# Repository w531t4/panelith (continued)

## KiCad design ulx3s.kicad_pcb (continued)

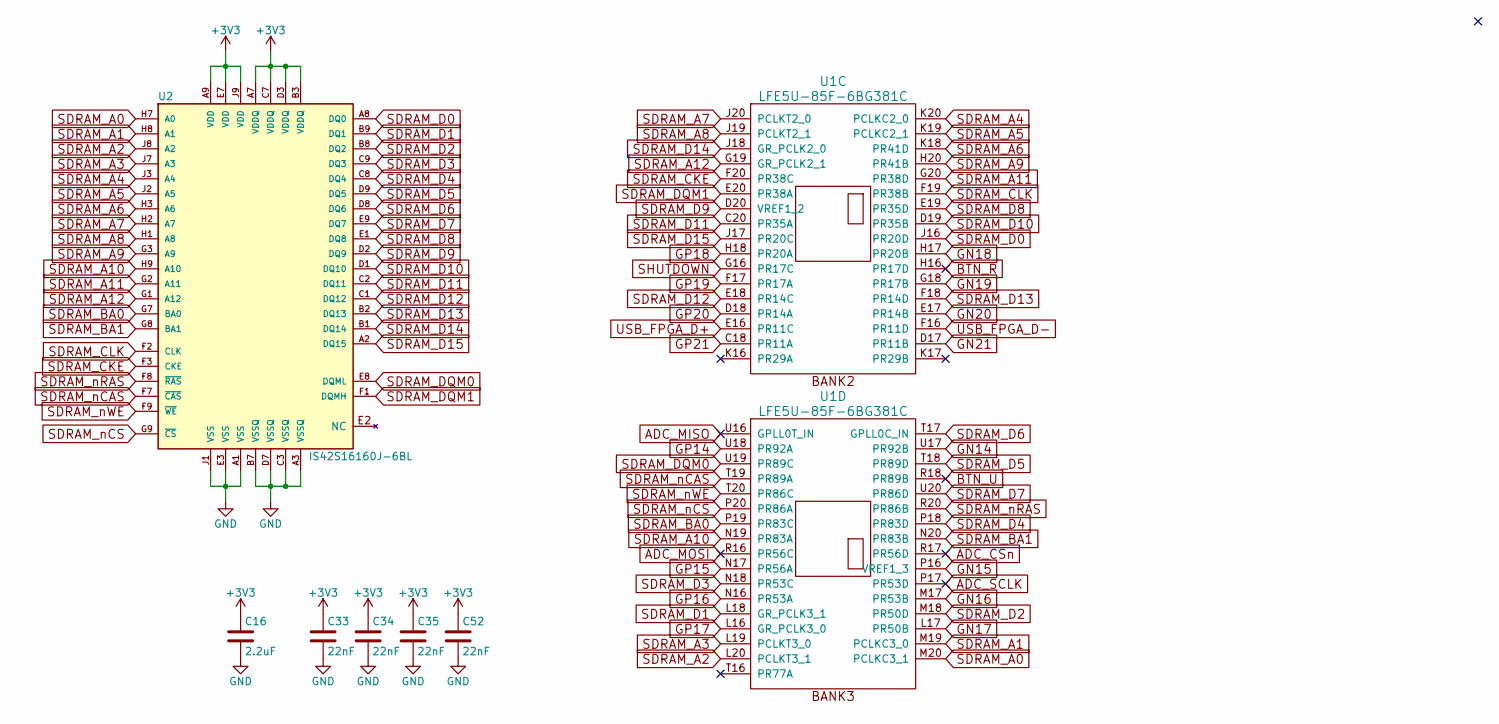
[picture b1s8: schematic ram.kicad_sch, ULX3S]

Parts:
C16: 2.2uF; C_0805_2012Metric; MPN CC0805MRX5R6BB225; LCSC C87995
C33, C34, C35, C52: 22nF; C_0603_1608Metric; MPN CC0603JRX7R8BB223; LCSC C107137
U1: LFE5U-85F-6BG381C; BGA-381_pitch0.8mm_dia0.4mm; MPN LFE5U-85F-6BG381C; LCSC C446029
U2: IS42S16160J-6BL; BGA54C80P9X9_800X800X120; MPN 870-42S16160J6BL; Mouser 870-IS42S16160G7TLTR

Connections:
+3V3: C16.1, C33.1, C34.1, C35.1, C52.1, U2.A7 (VDDQ), U2.A9 (VDD), U2.B3 (VDDQ), U2.C7 (VDDQ), U2.D3 (VDDQ), U2.E7 (VDD), U2.J9 (VDD); also elsewhere on the board
ADC_CSn: U1.R17 (PR56D)
ADC_MISO: U1.U16 (GPLL0T_IN)
ADC_MOSI: U1.R16 (PR56C)
ADC_SCLK: U1.P17 (PR53D)
BTN_R: U1.H16 (PR17D)
BTN_U: U1.R18 (PR89B)
GN14: U1.U17 (PR92B)
GN15: U1.P16 (VREF1_3)
GN16: U1.M17 (PR53B)
GN17: U1.L17 (PR50B)
GN18: U1.H17 (PR20B)
GN19: U1.G18 (PR17B)
GN20: U1.E17 (PR14B)
GN21: U1.D17 (PR11B)
GND: C16.2, C33.2, C34.2, C35.2, C52.2, U2.A1 (VSS), U2.A3 (VSSQ), U2.B7 (VSSQ), U2.C3 (VSSQ), U2.D7 (VSSQ), U2.E3 (VSS), U2.J1 (VSS); also elsewhere on the board
GP14: U1.U18 (PR92A)
GP15: U1.N17 (PR56A)
GP16: U1.N16 (PR53A)
GP17: U1.L16 (GR_PCLK3_0)
GP18: U1.H18 (PR20A)
GP19: U1.F17 (PR17A)
GP20: U1.D18 (PR14A)
GP21: U1.C18 (PR11A)
SDRAM_A0: U1.M20 (PCLKC3_1), U2.H7 (A0)
SDRAM_A1: U1.M19 (PCLKC3_0), U2.H8 (A1)
SDRAM_A2: U1.L20 (PCLKT3_1), U2.J8 (A2)
SDRAM_A3: U1.L19 (PCLKT3_0), U2.J7 (A3)
SDRAM_A4: U1.K20 (PCLKC2_0), U2.J3 (A4)
SDRAM_A5: U1.K19 (PCLKC2_1), U2.J2 (A5)
SDRAM_A6: U1.K18 (PR41D), U2.H3 (A6)
SDRAM_A7: U1.J20 (PCLKT2_0), U2.H2 (A7)
SDRAM_A8: U1.J19 (PCLKT2_1), U2.H1 (A8)
SDRAM_A9: U1.H20 (PR41B), U2.G3 (A9)
SDRAM_A10: U1.N19 (PR83A), U2.H9 (A10)
SDRAM_A11: U1.G20 (PR38D), U2.G2 (A11)
SDRAM_A12: U1.G19 (GR_PCLK2_1), U2.G1 (A12)
SDRAM_BA0: U1.P19 (PR83C), U2.G7 (BA0)
SDRAM_BA1: U1.N20 (PR83B), U2.G8 (BA1)
SDRAM_CKE: U1.F20 (PR38C), U2.F3 (CKE)
SDRAM_CLK: U1.F19 (PR38B), U2.F2 (CLK)
SDRAM_D0: U1.J16 (PR20D), U2.A8 (DQ0)
SDRAM_D1: U1.L18 (GR_PCLK3_1), U2.B9 (DQ1)
SDRAM_D2: U1.M18 (PR50D), U2.B8 (DQ2)
SDRAM_D3: U1.N18 (PR53C), U2.C9 (DQ3)
SDRAM_D4: U1.P18 (PR83D), U2.C8 (DQ4)
SDRAM_D5: U1.T18 (PR89D), U2.D9 (DQ5)
SDRAM_D6: U1.T17 (GPLL0C_IN), U2.D8 (DQ6)
SDRAM_D7: U1.U20 (PR86D), U2.E9 (DQ7)
SDRAM_D8: U1.E19 (PR35D), U2.E1 (DQ8)
SDRAM_D9: U1.D20 (VREF1_2), U2.D2 (DQ9)
SDRAM_D10: U1.D19 (PR35B), U2.D1 (DQ10)
SDRAM_D11: U1.C20 (PR35A), U2.C2 (DQ11)
SDRAM_D12: U1.E18 (PR14C), U2.C1 (DQ12)
SDRAM_D13: U1.F18 (PR14D), U2.B2 (DQ13)
SDRAM_D14: U1.J18 (GR_PCLK2_0), U2.B1 (DQ14)
SDRAM_D15: U1.J17 (PR20C), U2.A2 (DQ15)
SDRAM_DQM0: U1.U19 (PR89C), U2.E8 (DQML)
SDRAM_DQM1: U1.E20 (PR38A), U2.F1 (DQMH)
SDRAM_nCAS: U1.T19 (PR89A), U2.F7 (~CAS)
SDRAM_nCS: U1.P20 (PR86A), U2.G9 (~CS)
SDRAM_nRAS: U1.R20 (PR86B), U2.F8 (~RAS)
SDRAM_nWE: U1.T20 (PR86C), U2.F9 (~WE)
SHUTDOWN: U1.G16 (PR17C)
USB_FPGA_D+: U1.E16 (PR11C); also elsewhere on the board
USB_FPGA_D-: U1.F16 (PR11D); also elsewhere on the board

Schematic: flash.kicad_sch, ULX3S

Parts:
D28: 1N914; D_SOD-323_HandSoldering; MPN 1N4148WS; Digike_y 1N4148WXTPMSCT-ND; not fitted
D29: 1N914; D_SOD-323_HandSoldering; MPN 1N4148WS; LCSC C258181
R11: 10k; R_0603_1608Metric; MPN RC0603FR-0710KL; Mouser 603-RC0603FR-0710KL
R12, R27, R28: 10k; R_0603_1608Metric; MPN RC0603FR-0710KL; LCSC C15401
R29: 1.1k; R_0603_1608Metric; MPN 13-AC0603FR-071K1LCT-ND; Digikey 13-AC0603FR-071K1LCT-ND
R30: 4.7k; R_0603_1608Metric; MPN 603-RC0603FR-074K7L; LCSC C218056
R31, R32, R33: 15k; R_0603_1608Metric; MPN RC0603FR-0715KL; LCSC C217750
U1: LFE5U-85F-6BG381C; BGA-381_pitch0.8mm_dia0.4mm; MPN LFE5U-85F-6BG381C; LCSC C446029
U10: IS25LP128F-JBLE; SOA008-150-208mil; MPN IS25LP128F-JBLE; Mouser 454-W25Q128JVSIMTR

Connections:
+3V3: R11.1, R12.1, R27.1, R28.1, R29.1, R30.1, R31.1, R32.1, R33.1, U1.T2 (SN/CSn), U1.T3 (WRITEn), U1.T4 (CFG_1), U1.U2 (CS1n), U10.8 (VCC); also elsewhere on the board
/flash/FLASH_MISO: R28.2, U1.V2 (D1/MISO), U10.2 (MISO)
/flash/FLASH_MOSI: R27.2, U1.W2 (D0/MOSI), U10.5 (MOSI)
/flash/FLASH_SCK: R29.2, U1.U3 (CCLK), U10.6 (SCK)
/flash/FLASH_nCS: R30.2, U1.R2 (CSSPIN), U10.1 (~CS)
/flash/FLASH_nHOLD: R12.2, U1.W1 (D3/HOLDn), U10.7 (~HOLD)
/flash/FLASH_nWP: R11.2, U1.Y2 (D2/WPn), U10.3 (~WP)
/flash/FPGA_DONE: R32.2, U1.Y3 (DONE)
/flash/FPGA_INITN: R33.2, U1.V3 (INITn)
/flash/FPGA_PROGRAMN: D28.2 (A), D29.2 (A), R31.2, U1.W3 (PROGRAMn)
BTN_D: U1.V1 (D4/MOSI2)
BTN_F1: U1.R1 (D7)
BTN_F2: U1.T1 (D6)
BTN_L: U1.U1 (D5/MISO2)
BTN_PWRn: D28.1 (K); also elsewhere on the board
GND: U1.R4 (CFG_2), U1.U4 (CFG_0), U10.4 (GND); also elsewhere on the board
USER_PROGRAMN: D29.1 (K); also elsewhere on the board

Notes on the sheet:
PWRBTn on "power" sheet
BTN_U v1.7
For programming Flash thru JTAG see Lattice FPGA-TN-02050
NC v1.7
pullups to allow entering USER mode TN1260: lattice ECP5 sysCONFIG guide p.6, p.8, p.13
CFG select Master SPI (MSPI) TN1260: lattice ECP5 sysCONFIG guide p.17
BTN_R v1.7
USER_PROGRAMN on "usb" sheet
Deviation from TN1260 in pullup: values for BOM simplification. Correct values should be 1k but 1.1k is used.
pullups for Master SPI (MSPI) required by TN1260: lattice ECP5 sysCONFIG guide p.6

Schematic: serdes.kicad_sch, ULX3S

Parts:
U1: LFE5U-85F-6BG381C; BGA-381_pitch0.8mm_dia0.4mm; MPN LFE5U-85F-6BG381C; Mouser 842-LFE5U85F6BG381C

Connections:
/serdes/STXN11: U1.W18 (HDTXN0_D1CH1)
/serdes/STXP11: U1.W17 (HDTXP0_D1CH1)
GND: U1.T6 (VCCA0), U1.T7 (VCCHTX0_D0CH0), U1.T8 (VCCHRX0_D0CH0), U1.T9 (VCCHRX0_D0CH1), U1.T10 (VCCHTX0_D0CH1), U1.T11 (VCCHTX0_D1CH0), U1.T12 (VCCHRX0_D1CH0), U1.T13 (VCCHRX0_D1CH1), U1.T14 (VCCHTX0_D1CH1), U1.T15 (VCCA1), U1.U6 (VCCA0), U1.U15 (VCCA1), U1.V10 (VCCAUXA0), U1.V11 (VCCAUXA0), U1.V17 (VCCAUXA1), U1.V18 (VCCAUXA1), U1.W20 (REFCLKN_D1), U1.Y14 (HDRXP0_D1CH0), U1.Y15 (HDRXN0_D1CH0), U1.Y19 (REFCLKP_D1); also elsewhere on the board

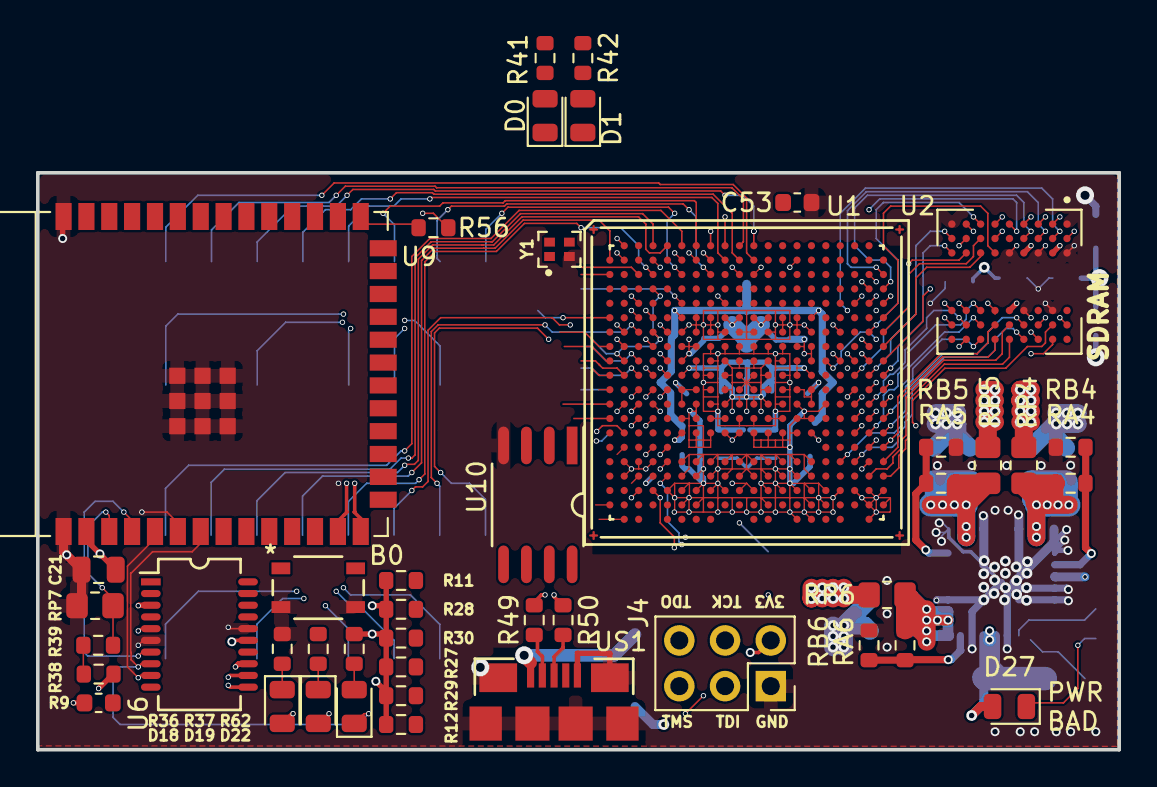
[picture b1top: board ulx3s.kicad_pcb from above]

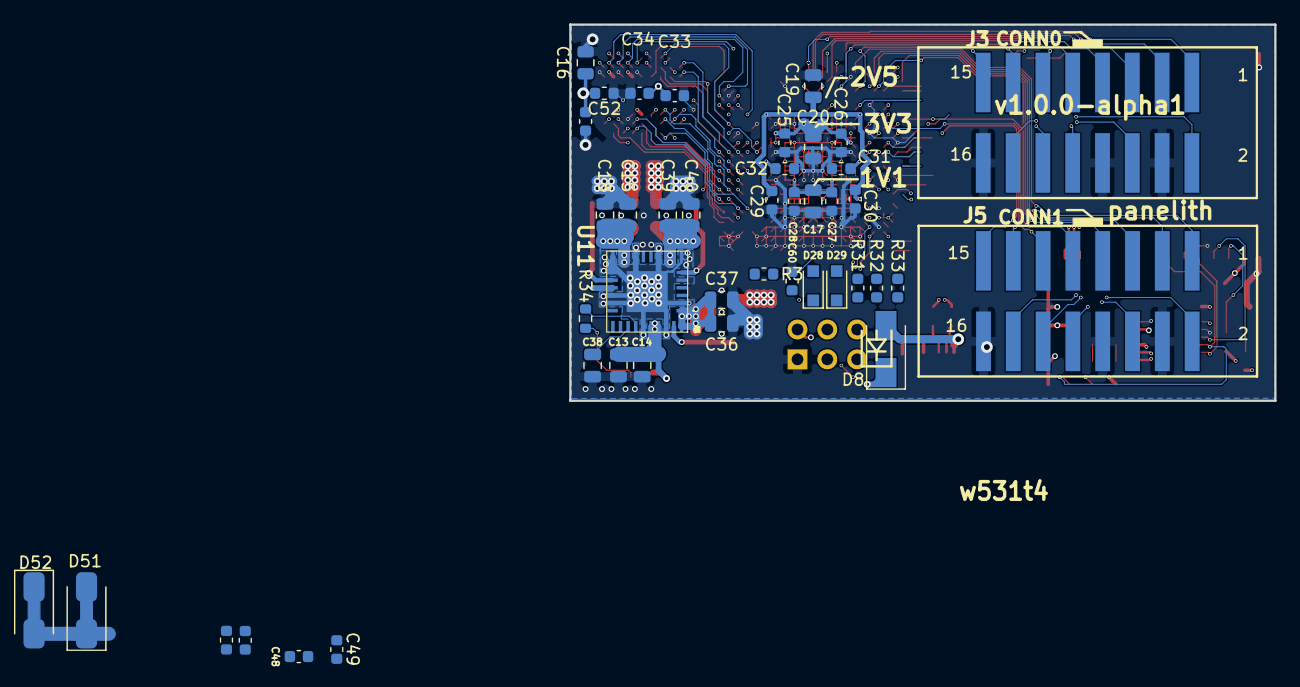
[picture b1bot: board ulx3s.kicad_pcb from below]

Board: 8 copper layers, 60.1 x 32.0 mm, 87 parts (43 on the bottom side), 141 nets.

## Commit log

2026-04-30 convert old kicad to 9
2026-04-30 ignore backup dir
2026-04-30 update pcb from schematic
2026-04-30 update rescue lib
2026-04-30 upgrade lib: lfe5bg381
2026-04-30 update lib: ft2232
2026-04-30 upgrade lib esp32
2026-04-30 update lib ssd_13xx
2026-04-30 update lib ftdi
2026-04-30 updated lib max1112x
2026-04-30 updated lib micro_sd_card_cd
2026-04-30 updated lib mt48lc16m16a2tg
2026-04-30 updated lib usb_otg
2026-04-30 updated lib dcdc
2026-04-30 updated lib hdmi-d
2026-04-30 updated lib jack_trs_6pins
2026-04-30 updated lib jack_trs_6pins_apple
2026-04-30 updated lib pca9306d
2026-04-30 updated lib st7789
2026-04-30 update lib 104031-0811
2026-04-30 added PWR_PIN to analog ADC_3.3v
2026-04-30 remove previous backups
2026-04-30 fix: incorrect pin types for max1112x
2026-04-30 omit .bak files from footprints dir
2026-04-30 add PWR_PIN to RTCVDD
2026-04-30 add pwr_pin to 2.5v
2026-04-30 add pwr_pin to 1.1v
2026-04-30 add pwr_pin to 5v
2026-04-30 add pwr_flag to VREF2
2026-04-30 add pwr_flag to SD3V3
2026-04-30 add pwr_flag to +3V3
2026-04-30 remove .bak files
2026-04-30 update ref-/ref+ pins to passive (erc) max11125
2026-04-30 update pin4 on usb-micro connector to passive
2026-04-30 mark DOUT/CSOn as not-connected
2026-04-30 fix: broken crystal pinout after github: 5286
2026-04-30 make PT20A no-connect
2026-04-30 make GR_PCLK1_0 no-connect
2026-04-30 update directionality of some fgpa pins
2026-04-30 push schematic changes to pcb
2026-04-30 update constraints
2026-04-30 add more constraints
2026-05-01 fix: fill space broken because of netlist constraints
2026-05-01 ignore lck files
2026-05-01 fix: issue with mask for jumper:D_SMA_Jumper_NC
2026-05-01 fix: update geometry error with mask for R_0805_2012Metric_Pad1.29x1.40mm_HandSolder_Jumper_NC
2026-05-01 allow bridged solder mask aperatures between pads within footprints
2026-05-01 remove leftover .bak files
2026-05-01 Remove old project files
2026-05-01 reposition resistor to avoid drc error
2026-05-01 reposition d28/d29 to meet spacing
2026-05-01 fix: only one connection to mounting hole near esp32 on bottom,u2
2026-05-01 add empty lib socket_strips
2026-05-01 save end-connectors to socket_strips. update footprint in schematic, push schem to pcb
2026-05-01 use .3mm border around thermal-relief square edge connector pads
2026-05-01 add via to provide gnd to isolated island on j3
2026-05-01 GDPI1 fix island with via
2026-05-01 reposition J3 to allow for more than one thermal relief
2026-05-01 remove exlusion zone to allow for extra thermal relief to C48 pad 2
2026-05-01 fix missing relief line to c30 pad 2
2026-05-01 fix missing relief line to j4 p1
2026-05-01 modify d21 pad 2 to allow for additional thermal relief track
2026-05-01 Remove exlusion zone to assist C56/C55's ground pads get an extra relief leg
2026-05-01 reposition C30 so that D20 pinA can get another thermal relief leg
2026-05-01 annotate a few exceptions related to relief
2026-05-01 remove an exclusion zone to assist c25/c26 get to another thermal relief leg
2026-05-01 fix a 'item shorting two nets' issue on d51/52 - deliberate
2026-05-01 fix a 'item shorting two nets' issue on d9 - deliberate
2026-05-01 fix a 'item shorting two nets' issue on rp3 - deliberate
2026-05-01 add exceptions for deliberate net jumps for user config
2026-05-01 update warning/error toggles
2026-05-01 fix clearance violation
2026-05-01 add exception for another thing with user-servicable pads
2026-05-01 resolve some unconnected end errors
2026-05-01 remove unused via
2026-05-01 remove unconnected track
2026-05-01 re-run usb_fpga_d- do use individual traces
2026-05-01 fix footprint for LCD1 (pad4)
2026-05-01 add mounting_holes local lib
2026-05-01 copy footprint to local repo
2026-05-02 remove unneeded components from schema
2026-05-02 immediately after - update pcb from schematic
2026-05-02 remove a few more oled things
2026-05-02 resolve errors
2026-05-02 update constraints, don't apply them yet
2026-05-02 ignore kicad prl
2026-05-02 jlcpcb
2026-05-02 update track widths, begin routing paths
2026-05-02 rewire all the things
2026-05-02 remove btn_r, clean trace/via
2026-05-02 mark other button as no-connect, remove tracks
2026-05-02 moving more wires
2026-05-02 update silkscreen
2026-05-02 start to normalize bom
2026-05-02 updating part numbers across schematcs
2026-05-02 switched from STPS2L30AF to STPS2L30A
2026-05-02 migrate ram from MT48LC16M16A2TG-6A to IS42S16160J-6TL
2026-05-02 update mpn at mouser/digikey for 2N7002
2026-05-02 switch from NSR0530HT1G to BAT54WSQ-7-F
2026-05-02 adjust mouser part number of BC857 to 757-TBC857BLM
2026-05-02 switch to FT231XS (not Q) - rewire for SSOP-20
2026-05-03 initial s3 stuff
2026-05-03 upgrade to kicad10
2026-05-03 update datasheet for ram
2026-05-03 update url to ftdi datasheet
2026-05-03 fix footprint/symbol for ft231- need to re-work routing
2026-05-03 add colors to JTAG/FTDI nets
2026-05-03 mark all extra pins as no-connect. erc fixed.
2026-05-03 remove 433mhz ant
2026-05-03 rewire of ft231 complete
2026-05-03 set more reasonable copper->edge. fix 3v3 pin not-attached. fix overlayed via
2026-05-04 add net classes
2026-05-04 remove a few unused pins
2026-05-04 add missing nets to DIFF
2026-05-04 update track for usb. reposition ftdi
2026-05-04 add rules for differential pair USB
2026-05-04 add rules for sdram skew
2026-05-04 add some more netclasses
2026-05-04 rewire J1 bus. move buttons up. move some more voltage stuff to In1.cu
2026-05-04 reposition led's
2026-05-04 reposition flash
2026-05-04 make a few via's larger
2026-05-04 reposition f1/f2 buttons
2026-05-05 rework esp area again, due to incorrect footprint. add some netclass rules. put esp32 and ftdi on front of board
2026-05-05 drc good
2026-05-05 v0.0.1
2026-05-05 add corner holes to paste layer for stencil alignment
2026-05-05 use substitution with page attributes for silkscreen
2026-05-05 fix drc issue
2026-05-05 still use extra stencil paste hole, but use through-hole marker again
2026-05-05 bump version
2026-05-06 0.0.4
2026-05-06 move 3 led's to front of board
2026-05-06 cleanup tracks
2026-05-06 0.0.5
2026-05-06 0.0.6 - fix footprint of four circles
2026-05-07 Remove 'Leave Empty' in favor of using attributes
2026-05-07 add web bom for 0.0.6
2026-05-07 remove wake up/shutdown logic
2026-05-07 add 0ohm resistor to bom for RV3
2026-05-07 removed optional 2.5 on J1
2026-05-07 remove analog schematic
2026-05-07 remove buttons f1/f2
2026-05-07 remove hanging track
2026-05-07 reposition clock to top of board
2026-05-07 reposition 3v3 lines around flash resistors/IC
2026-05-07 remove extra 3v3 bar. extend rule area to cover j1
2026-05-08 remove ref. to 2.5v on rear silkscreen
2026-05-09 add courtyard to bga381
2026-05-09 update schematic with new footprint for ram. pre-wiring the ram on pcb
2026-05-10 route wires to BGA SDRAM
2026-05-10 add MPM54304 to symbol/footprints
2026-05-10 update MPM54304 symbol
2026-05-10 update symbol again
2026-05-10 update symbol for new psu
2026-05-10 replace psu symbol for new device... haven't yet pushed to pcb
2026-05-10 fixed missing PxVx nets
2026-05-11 replaced psu, need to still to drc
2026-05-11 remaining thing: i2c connector
2026-05-11 close off i2c, too fragile
2026-05-11 update parts for 22uf/1uf. Update footprint for RP* items
2026-05-12 move memory closer to fpga
2026-05-12 fix some drc issues
2026-05-12 interim esp32 change
2026-05-12 more wifi
2026-05-12 remove extra schematic page for esp32
2026-05-13 reposition flash to bottom. route esp32-s3. fix drc issues
2026-05-13 add silkscreen border around power chip
2026-05-13 remove serdes. fix led connectivity issues
2026-05-21 add hub75 connector to libraries
2026-05-21 update footprint for hub75
2026-05-21 remove legacy esp32 from schematic
2026-05-21 remove US2 port
2026-05-22 add ecs-1612mv part
2026-05-22 remove extra sheet for alt fpga
2026-05-22 switch to new oscillator
2026-05-22 remove stale rule area (from US2)
2026-05-22 add footprint for smaller pts810 button
2026-05-22 make pts810 use 1/1/2/2 layout instead of 1/2/3/4
2026-05-22 switch to smaller pts810 button
2026-05-23 add some comment labels to power plane nets
2026-05-23 broken: shrink board, re-orient parts. mid-progress, before 4-6 layer
2026-05-23 reassign j1 signals
2026-05-24 in progress, placement happend -- working on wiring
2026-05-24 attempting to route memory, moved to 8layer
2026-05-24 memory is wired
2026-05-24 routed conn1
2026-05-25 finished routing conn1/conn2
2026-05-25 routed power
2026-05-25 routed jtag, partial ftdi
2026-05-26 done with routing
2026-05-26 done with drc
2026-05-26 update text markings
2026-05-26 bump board to panelith v1.0.1
2026-05-26 move to v1.0.2 - use 0.09mm default trace
2026-05-26 update board stackup
2026-05-26 fix diff pairs
2026-05-26 add i2c header
2026-05-27 fix drc for differential traces
2026-05-27 bump to v1.0.3
2026-05-27 changes label positions for flash pullups
2026-05-27 switch to usb-c. upgrade to v1.0.4
2026-05-27 add fids, add attributions on board, bump to v1.0.5
2026-05-27 bump v1.0.6 - remove exclude area
2026-05-27 fix exclude zone, drc. v1.0.7
2026-05-27 this should have gone with the prev. commit
2026-05-27 make MPN reflect mouser part numbers
2026-06-02 shift usb right away from hub75
2026-06-02 add ground to i2c header
2026-06-04 add secondary power-only usb-c connector. v1.0.9
2026-06-04 v1.0.10 - changed wire slop to copper polygons
2026-06-04 update footprints to include additional border. add i2c resistors
2026-06-05 add new hub75 symbol
2026-06-05 update shematic for new hub75 connector
2026-06-05 fix board after move to new hub75 connector
2026-06-05 fix drc
2026-06-05 switch to pinheader for jtag in schematic
2026-06-05 Switch to TagConnect for JTAG
2026-06-05 add pwrbad indicator
2026-06-05 update bom fields
2026-06-05 update fields, add names to FIDS
2026-06-05 remove extra unnecessary symbol from hub75 footprint on rrear side
2026-06-05 don't populate 3pin i2c header
2026-06-05 attach 3d design to footprint
2026-06-05 add 3d file for flash
2026-06-05 update position of reference for ram
2026-06-05 update part numbers for us2
2026-06-05 v1.0.11
2026-06-06 moved hub75 closer together
2026-06-06 shift hub75 closer together, move and replace button
2026-06-07 add mounting holes. reposition ft231x. use nsleep
2026-06-07 fix proximity of gnd
2026-06-07 avoid via placement in cap/resistor gap
2026-06-07 manually use arcs in edge.cut. update half-hole footprint. remove cu x's from fpga footprint
2026-06-07 reposition usr led's to bottom
2026-06-07 fix schematic parity
2026-06-07 v1.0.13
2026-06-07 remove extra label from silkscreen
2026-06-07 v1.0.14 - respect 0.5mm max POVF via size. fix type of button.
2026-06-07 v1.0.15 - use explicit via sizes, add instructions per via size
2026-06-09 reposition holes near pmic
2026-06-09 v1.0.16 - switch via type. fix j/h issue.
2026-06-09 v1.0.17 - fix power layer v3.3 issue. readjust fpga zones so vias are fully covered
2026-06-13 v1.1.0
2026-06-18 use more via in pads
2026-06-21 remove stale stuff from repo
2026-06-22 remove schematics symlink
2026-06-22 remove more files
2026-06-22 update manuf. notes
2026-06-22 initial state for panelith lpf
